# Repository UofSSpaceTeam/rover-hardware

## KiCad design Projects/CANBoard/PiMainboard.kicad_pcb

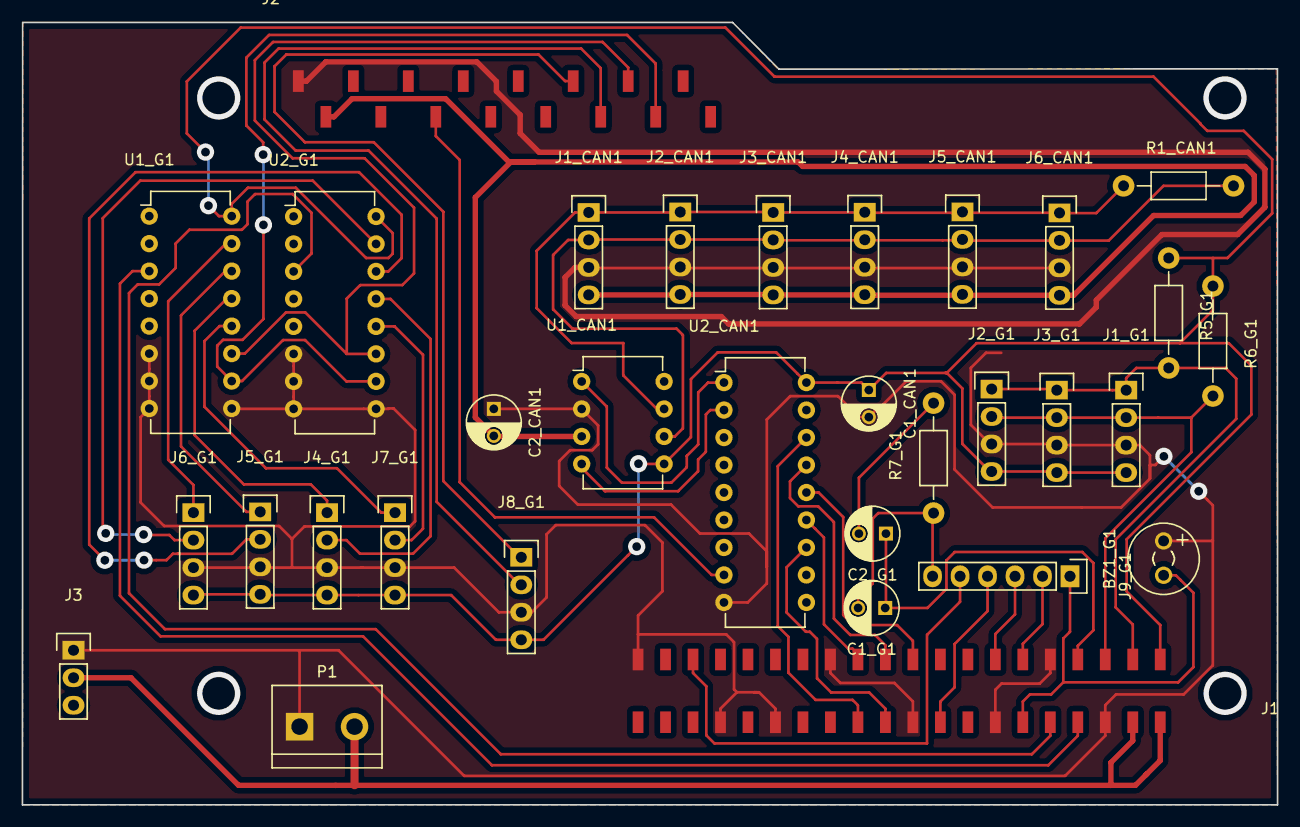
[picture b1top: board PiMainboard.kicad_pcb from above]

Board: 2 copper layers, 116.0 x 72.3 mm, 32 parts (0 on the bottom side), 37 nets.

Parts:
BZ1_G1: buzzer; MagneticBuzzer_Kingstate_KCG0601
C1_CAN1, C2_CAN1: 0.1uF; C_Radial_D5_L11_P2.5
C1_G1: 2.2pF; C_Radial_D5_L11_P2.5
C2_G1: 10pF; C_Radial_D5_L11_P2.5
J1: RasPI_IO_Header_B+; 40PinSMDFemaleSocket
J1_CAN1, J1_G1, J2_CAN1, J2_G1, J3_CAN1, J3_G1, J4_CAN1, J4_G1, J5_CAN1, J5_G1, J6_CAN1, J6_G1, J7_G1, J8_G1: HEADER_4; Pin_Header_Straight_1x04
J2: HEADER_16; 16PinSMDFemaleSocket
J3: HEADER_3; Pin_Header_Straight_1x03
J9_G1: HEADER_6; Pin_Header_Straight_1x06
P1: CONN_01X02; bornier2
R1_CAN1: 100; Resistor_Horizontal_RM10mm
R5_G1, R6_G1: 1k8; Resistor_Horizontal_RM10mm
R7_G1: 1k; Resistor_Horizontal_RM10mm
U1_CAN1: MCP2562; DIP-8_W7.62mm
U1_G1, U2_G1: 74HC4051; DIP-16_W7.62mm
U2_CAN1: MCP2515; DIP-18_W7.62mm

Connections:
3v3: C1_CAN1.1, J1.1, J1.17, J1_G1.4, J2_G1.4, J3_G1.4, J4_G1.4, J5_G1.4, J6_G1.4, J7_G1.4, J8_G1.4, R5_G1.1, R6_G1.1, U1_CAN1.5, U1_G1.16, U2_CAN1.18, U2_G1.16
5v0: C2_CAN1.2, J1.2, J1.4, J1_CAN1.4, J2.2, J2_CAN1.4, J3.2, J3_CAN1.4, J4_CAN1.4, J5_CAN1.4, J6_CAN1.4, P1.2, U1_CAN1.3
/CANBus/CANH_OUT: J1_CAN1.1, J2_CAN1.1, J3_CAN1.1, J4_CAN1.1, J5_CAN1.1, J6_CAN1.1, R1_CAN1.1, U1_CAN1.7
/CANBus/CANL_OUT: J1_CAN1.2, J2_CAN1.2, J3_CAN1.2, J4_CAN1.2, J5_CAN1.2, J6_CAN1.2, R1_CAN1.2, U1_CAN1.6
/CANBus/CE: J1.24, U2_CAN1.16
/CANBus/CLK16: J2.6, U2_CAN1.8
/CANBus/INT: J1.22, U2_CAN1.12
/CANBus/MISO: J1.21, U2_CAN1.15
/CANBus/MOSI: J1.19, U2_CAN1.14
/CANBus/SCLK: J1.23, U2_CAN1.13
/GPIOModule/FM: C1_G1.1, C2_G1.1, J1.7
/GPIOModule/GPIO17: J1.11, J9_G1.2
/GPIOModule/GPIO21: J1.13, J9_G1.3
/GPIOModule/GPIO24: J1.18, J9_G1.4
/GPIOModule/GPIO38: J2.13, U1_G1.11, U2_G1.11
/GPIOModule/GPIO39: J2.14, U1_G1.10, U2_G1.10
/GPIOModule/PWM0: BZ1_G1.1, J1.12, J9_G1.1
/GPIOModule/PWM1: J1.35, J9_G1.5
/GPIOModule/SCL: J1.5, J1_G1.2, J2_G1.2, J3_G1.2, R6_G1.2
/GPIOModule/SDA: J1.3, J1_G1.1, J2_G1.1, J3_G1.1, R5_G1.2
/GPIOModule/UART_RX0: J1.10, U2_G1.3
/GPIOModule/UART_RX0_0: J4_G1.2, U2_G1.13
/GPIOModule/UART_RX0_1: J5_G1.2, U2_G1.14
/GPIOModule/UART_RX0_2: J6_G1.2, U2_G1.15
/GPIOModule/UART_RX0_3: J7_G1.2, U2_G1.12
/GPIOModule/UART_RX1: J2.12, J8_G1.2
/GPIOModule/UART_TX0: J1.8, U1_G1.3
/GPIOModule/UART_TX0_0: J4_G1.1, U1_G1.13
/GPIOModule/UART_TX0_1: J5_G1.1, U1_G1.14
/GPIOModule/UART_TX0_2: J6_G1.1, U1_G1.15
/GPIOModule/UART_TX0_3: J7_G1.1, U1_G1.12
/GPIOModule/UART_TX1: J2.11, J8_G1.1
GND: BZ1_G1.2, C1_CAN1.2, C2_CAN1.1, J1.6, J1.9, J1.14, J1.20, J1.25, J1.30, J1.34, J1.39, J1_CAN1.3, J1_G1.3, J2.1, J2_CAN1.3, J2_G1.3, J3.1, J3_CAN1.3, J3_G1.3, J4_CAN1.3, J4_G1.3, J5_CAN1.3, J5_G1.3, J6_CAN1.3, J6_G1.3, J7_G1.3, J8_G1.3, P1.1, U1_CAN1.2, U1_G1.6, U1_G1.7, U1_G1.8, U1_G1.9, U2_CAN1.9, U2_G1.6, U2_G1.7, U2_G1.8, U2_G1.9
unnamed: C1_G1.2, J9_G1.6, R7_G1.1
unnamed: C2_G1.2, R7_G1.2
unnamed: U1_CAN1.1, U2_CAN1.1
unnamed: U1_CAN1.4, U2_CAN1.2

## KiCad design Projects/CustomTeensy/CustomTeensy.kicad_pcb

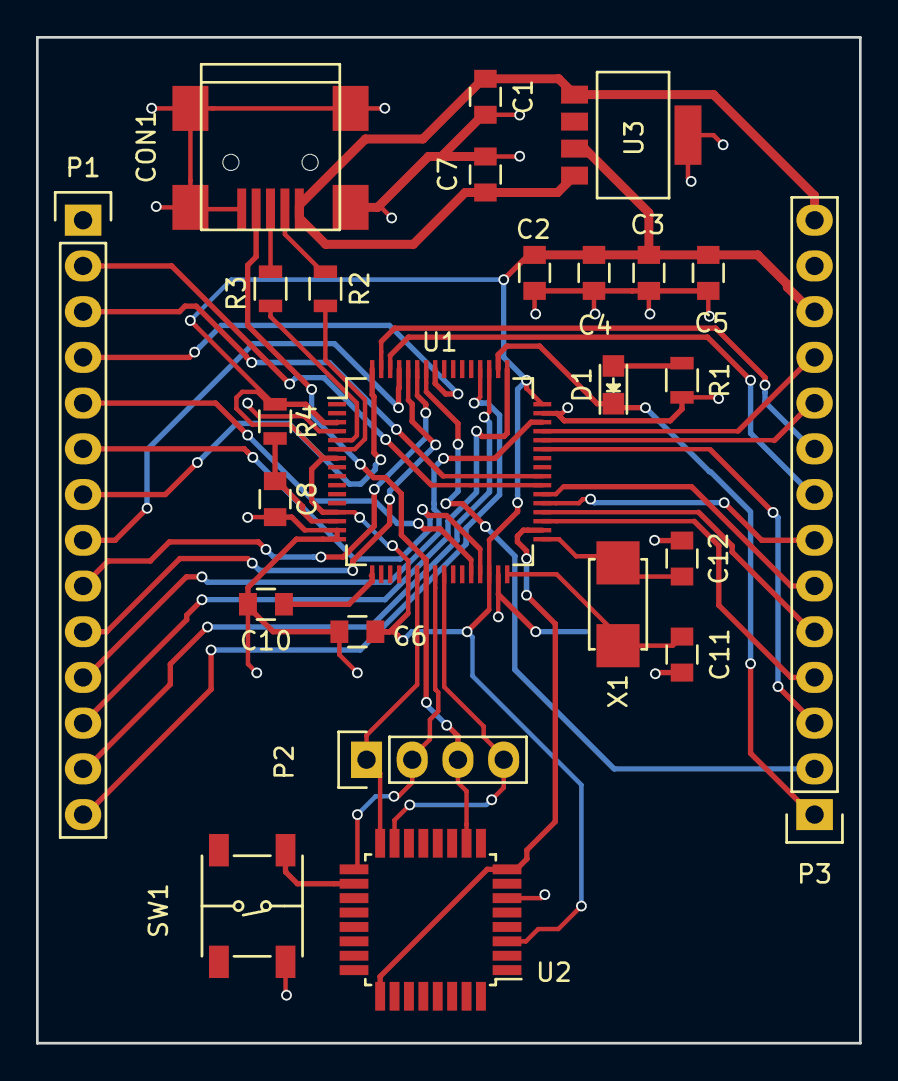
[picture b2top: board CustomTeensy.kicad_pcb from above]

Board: 2 copper layers, 45.7 x 55.9 mm, 25 parts (0 on the bottom side), 42 nets.

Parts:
C1, C2, C6, C7: 2.2uF; C_0805
C3, C4, C5, C8, C10: 0.1uF; C_0805
C11, C12: 20pF; C_0805
CON1: USB-MINI-B; USB_Mini-B
D1: LED; LED_0805
P1, P3: CONN_14; Pin_Header_Straight_1x14
P2: CONN_4; Pin_Header_Straight_1x04
R1, R4: 470; R_0805
R2, R3: 33; R_0805
SW1: SW_PUSH; Sparkfun_SMT_push_button
U1: mk20dx256vlh7; LQFP-64_10x10mm_Pitch0.5mm
U2: MKL04Z32_TQFP32; TQFP-32_7x7mm_Pitch0.8mm
U3: LP38693; SOT-223_5-pin
X1: CRYSTAL; ABM3_SMD_crystal

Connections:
+3.3V: C2.1, C3.1, C4.1, C5.1, C6.1, P3.12, R4.1, U1.3, U1.7, U1.13, U1.21, U1.30, U1.48, U2.3, U3.3
/D0: P1.2, U1.39
/D1: P1.3, U1.40
/D2: P1.4, U1.57
/D3: P1.5, U1.28
/D4: P1.6, U1.29
/D5: P1.7, U1.64
/D6: P1.8, U1.61
/D7: P1.9, U1.59
/D8: P1.10, U1.60
/D9: P1.11, U1.46
/D10: P1.12, U1.49
/D11: P1.13, U1.51
/D12: P1.14, U1.52
/D13: D1.1, P3.1, U1.50
/D14: P3.2, U1.58
/D15: P3.3, U1.43
/D16: P3.4, U1.35
/D17: P3.5, U1.36
/D18: P3.6, U1.38
/D19: P3.7, U1.37
/D20: P3.8, U1.62
/D21: P3.9, U1.63
/D22: P3.10, U1.44
/D23: P3.11, U1.45
/JTAG_TCLK: P2.1, U1.22, U2.16
/JTAG_TDI: CON1.4, P2.3, U1.23, U2.10
/JTAG_TDO: P2.2, U1.24, U2.17
/JTAG_TMS: P2.4, U1.25, U2.15
/Prog: SW1.1, U2.18
/Reset: U1.34, U2.8, U2.25
GND: C1.2, C2.2, C3.2, C4.2, C5.2, C6.2, C7.2, C8.2, C10.2, C11.2, C12.2, CON1.5, CON1.6, P1.1, P3.13, R1.2, SW1.2, U1.4, U1.15, U1.16, U1.31, U1.47, U2.6, U3.5
unnamed: C10.1, U1.17
unnamed: C11.1, U1.32, X1.1
unnamed: C12.1, U1.33, X1.2
unnamed: CON1.2, R2.1
unnamed: CON1.3, R3.1
unnamed: D1.2, R1.1
unnamed: R2.2, U1.6
unnamed: R3.2, U1.5
VREFH: C8.1, R4.2, U1.14
VUSB: C1.1, C7.1, CON1.1, P3.14, U3.1, U3.4
